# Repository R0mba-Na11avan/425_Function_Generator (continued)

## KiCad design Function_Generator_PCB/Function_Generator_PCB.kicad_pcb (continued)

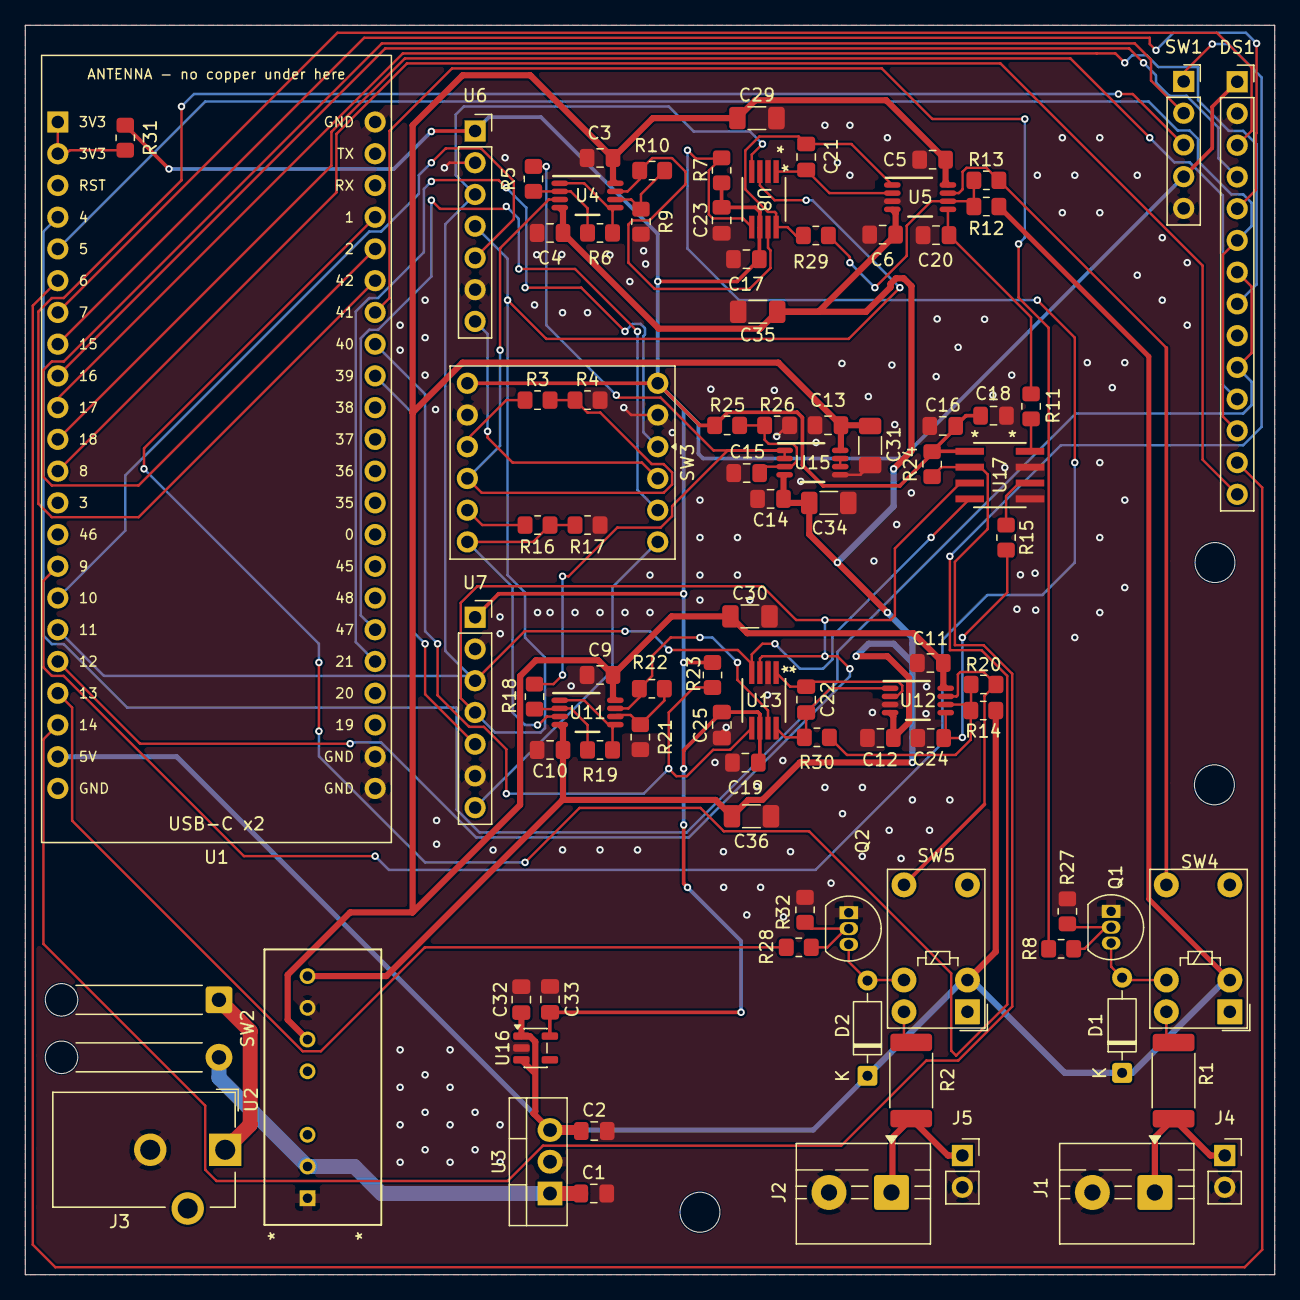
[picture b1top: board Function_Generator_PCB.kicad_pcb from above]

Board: 2 copper layers, 100.0 x 100.0 mm, 92 parts (0 on the bottom side), 68 nets.
